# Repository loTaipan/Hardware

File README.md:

#Hardware

This repo contains the hardware design.

The idea was to have it compatible with the original pyboard, since this piece of hard and software is jus..

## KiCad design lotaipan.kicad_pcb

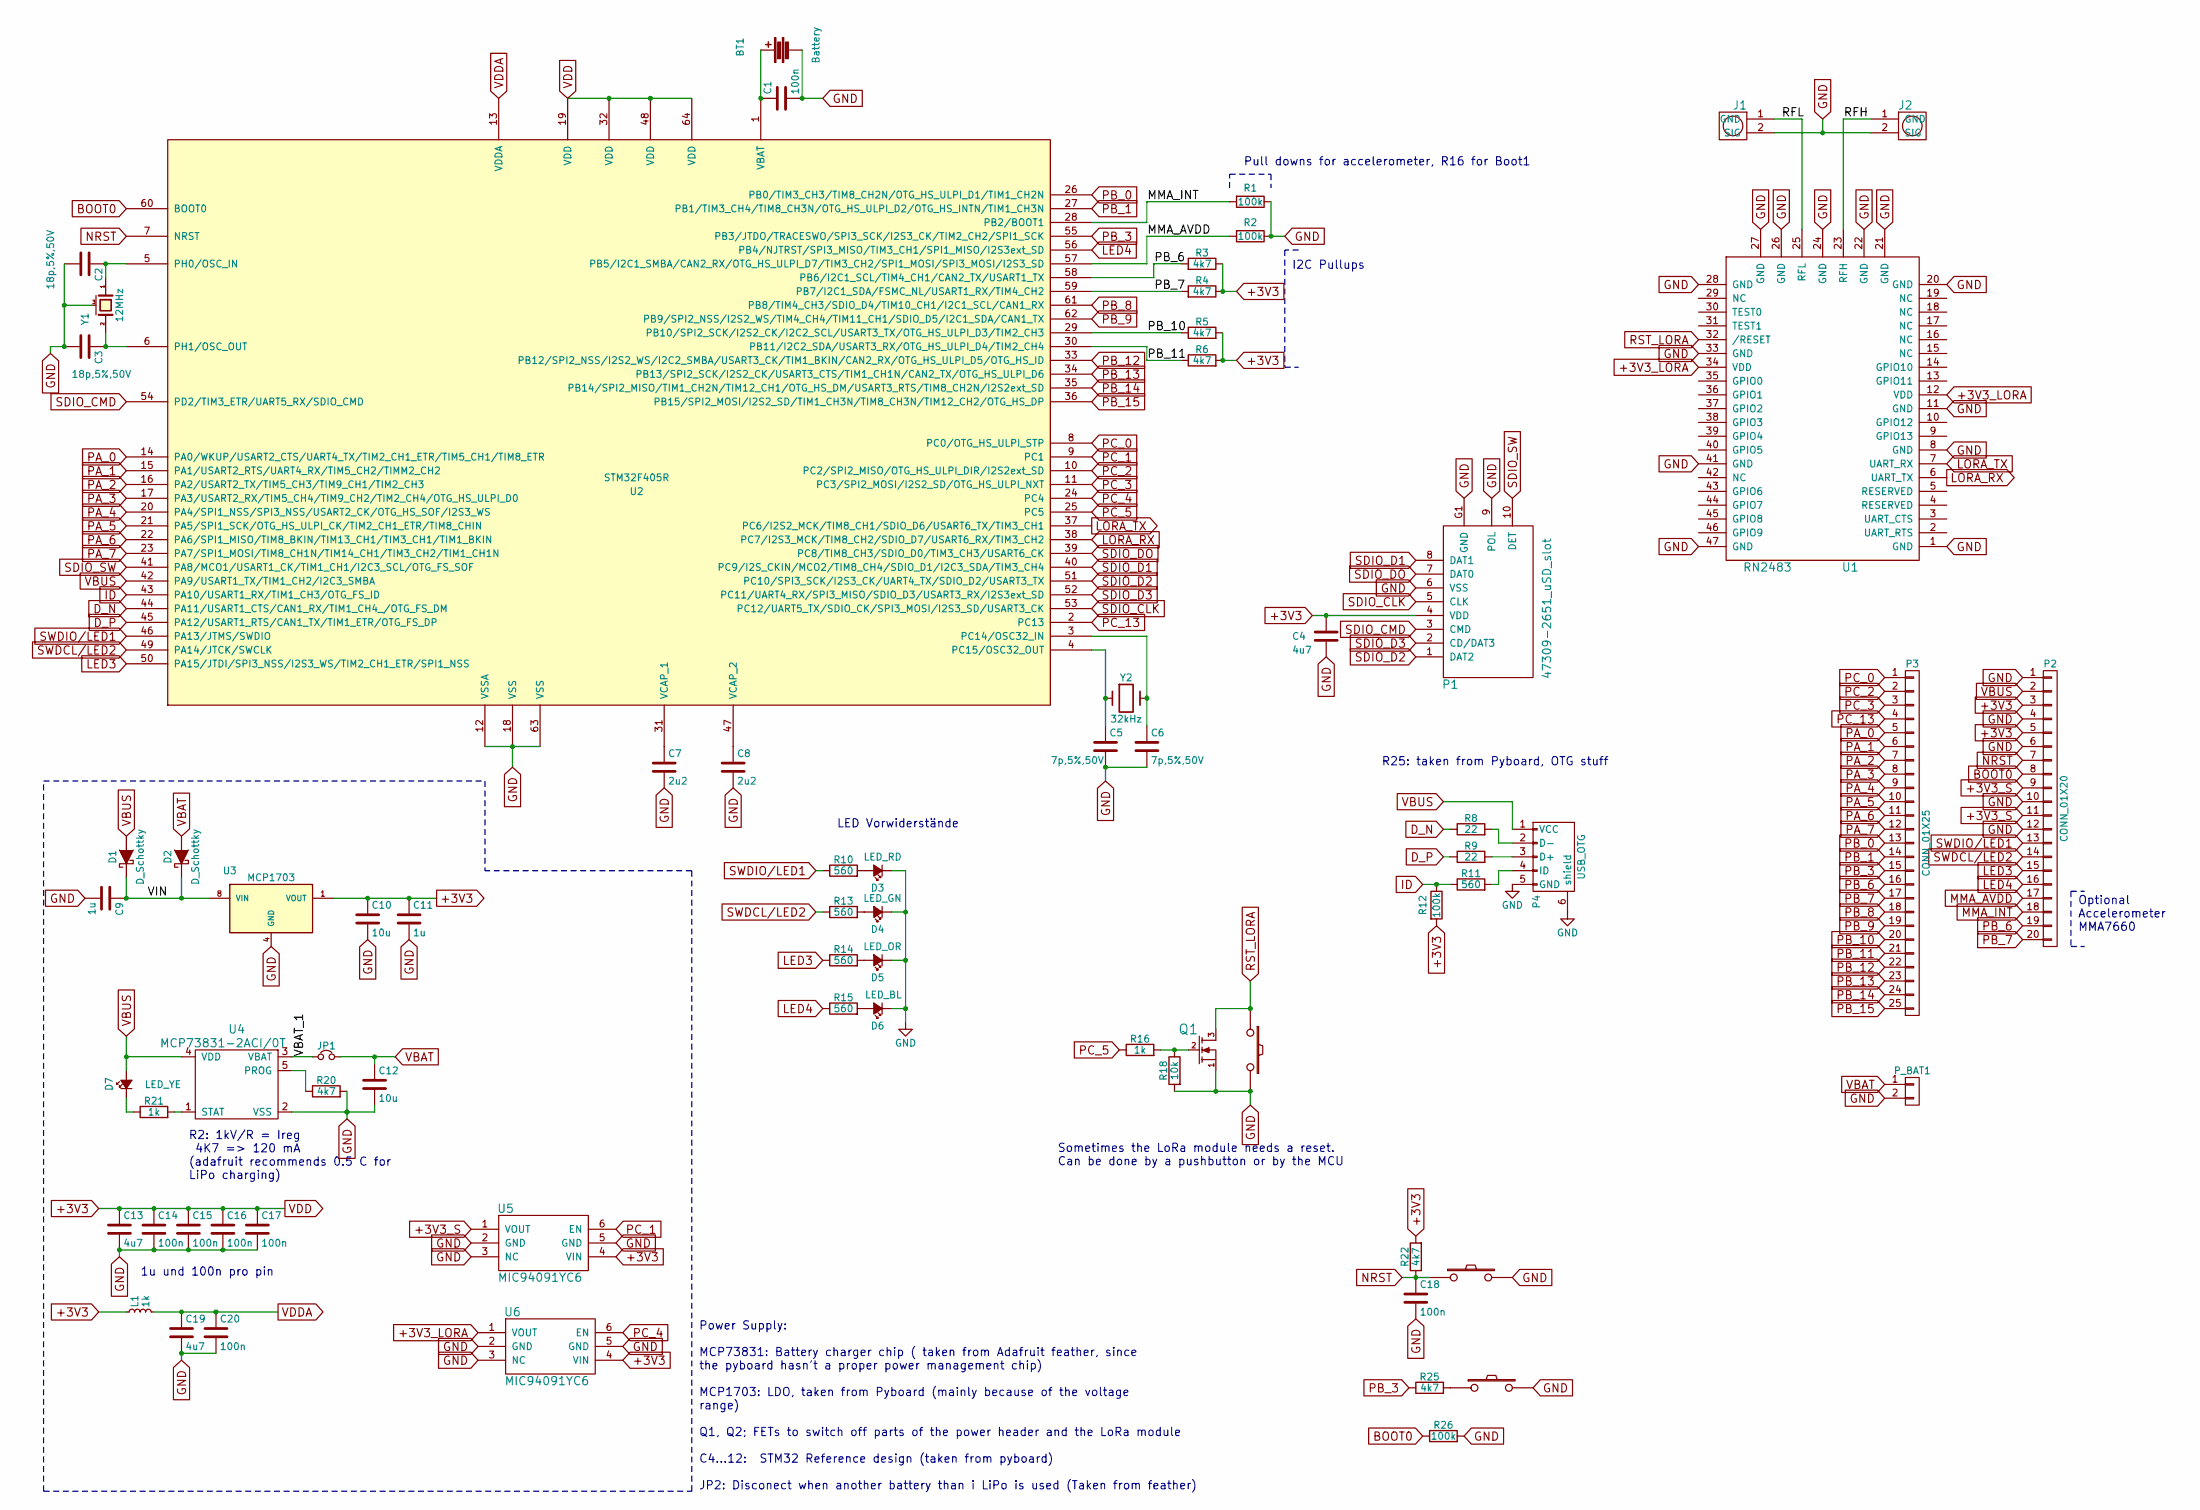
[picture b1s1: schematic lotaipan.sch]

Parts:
BT1: Battery; SparkFun-BATTERY_20MM_PTH_COMPACT
C1, C14, C15, C16, C17, C18, C20: 100n; C_0402
C2, C3: 18p,5%,50V; C_0402
C4, C13, C19: 4u7; C_0402
C5, C6: 7p,5%,50V; C_0402
C7, C8: 2u2; C_0402
C9, C11: 1u; C_0402
C10, C12: 10u; C_0402
D1, D2: D_Schottky; SOD-123
D3: LED_RD; Led_0603
D4: LED_GN; Led_0603
D5: LED_OR; Led_0603
D6: LED_BL; Led_0603
D7: LED_YE; Led_0603
J1, J2: SMA_through; coaxial_u.fl-r-smt-1
JP1: Jumper_NC_Small; SparkFun-SJ-NO
L1: 1k; inductor_smd_1008
P1: 47309-2651_uSD_slot; microsd_socket
P2: CONN_01X20; Pin_Header_Straight_1x20
P3: CONN_01X25; Pin_Header_Straight_1x25
P4: USB_OTG; conn_usb_B_micro_smd-2
P_BAT1: CONN_01X02; s2b-ph-kl
Q1: MOS_N_SGD; SOT-23
R1, R2, R12, R26: 100k; R_0402
R3, R4, R5, R6, R20, R22, R25: 4k7; R_0402
R8, R9: 22; R_0402
R10, R11, R13, R14, R15: 560; R_0402
R16, R21: 1k; R_0402
R18: 10k; R_0402
SW_RST1: SW_PUSH; smd_push
SW_RST_LORA1: SW_PUSH; smd_push
SW_USR1: SW_PUSH; smd_push
U1: RN2483
U2: STM32F405R; AB2_LQFP64
U3: MCP1703; dfn8-2x3
U4: MCP73831-2ACI/0T; sot23-5
U5, U6: MIC94091YC6; SC-70-6
Y1: 12MHz; crystal_FA238-TSX3225
Y2: 32kHz; ST3215SB32768C0HPWBB

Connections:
+3V3: C4.1, C10.1, C11.1, C13.1, C14.1, C15.1, C16.1, C17.1, L1.1, P1.4 (VDD), P2.3, P2.5, R3.1, R4.1, R5.2, R6.2, R12.2, R22.2, U2.19 (VDD), U2.32 (VDD), U2.48 (VDD), U2.64 (VDD), U3.1 (VOUT), U5.4 (VIN), U6.4 (VIN)
+3V3_LORA: U1.12 (VDD), U1.34 (VDD), U6.1 (VOUT)
+3V3_S: P2.9, P2.11, U5.1 (VOUT)
/RFH: J2.1 (GND), U1.23 (RFH)
/RFL: J1.1 (GND), U1.25 (RFL)
/VBAT_1: JP1.1, U4.3 (VBAT)
/VIN: C9.1, D1.1 (K), D2.1 (K), U3.8 (VIN)
BOOT0: P2.8, R26.1, U2.60 (BOOT0)
D_N: R8.1, U2.44 (PA11/USART1_CTS/CAN1_RX/TIM1_CH4_/OTG_F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)
D_P: R9.1, U2.45 (PA12/USART1_RTS/CAN1_TX/TIM1_ETR/OTG_FS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)
GND: BT1.2, C1.2, C2.2, C3.2, C4.2, C5.2, C6.2, C7.2, C8.2, C9.2, C10.2, C11.2, C12.2, C13.2, C14.2, C15.2, C16.2, C17.2, C18.2, C19.2, C20.2, D3.1 (K), D4.1 (K), D5.1 (K), D6.1 (K), J1.2 (SIG), J2.2 (SIG), P1.6 (VSS), P1.9 (POL), P1.G1 (GND), P2.1, P2.4, P2.6, P2.10, P2.12, P4.5 (GND), P4.6 (shield), P_BAT1.2, Q1.1 (S), R1.1, R2.1, R18.2, R20.2, R26.2, SW_RST1.2, SW_RST_LORA1.2, SW_USR1.2, U1.1 (GND), U1.8 (GND), U1.11 (GND), U1.20 (GND), U1.21 (GND), U1.22 (GND), U1.24 (GND), U1.26 (GND), U1.27 (GND), U1.28 (GND), U1.33 (GND), U1.41 (GND), U1.47 (GND), U2.12 (VSSA), U2.18 (VSS), U2.63 (VSS), U3.4 (GND), U4.2 (VSS), U5.2 (GND), U5.3 (NC), U5.5 (GND), U6.2 (GND), U6.3 (NC), U6.5 (GND), Y1.3 (case)
ID: R11.1, R12.1, U2.43 (PA10/USART1_RX/TIM1_CH3/OTG_FS_ID)
LED3: P2.15, R14.1, U2.50 (PA15/JTDI/SPI3_NSS/I2S3_WS/TIM2_CH1_ETR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)
LED4: P2.16, R15.1, U2.56 (PB4/NJTRST/SPI3_MISO/TIM3_CH1/SPI1_MISO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)
LORA_RX: U1.6 (UART_TX), U2.38 (PC7/I2S3_MCK/TIM8_CH2/SDIO_D7/USART6_RX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)
LORA_TX: U1.7 (UART_RX), U2.37 (PC6/I2S2_MCK/TIM8_CH1/SDIO_D6/USART6_TX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)
MMA_AVDD: P2.17, R2.2, U2.57 (PB5/I2C1_SMBA/CAN2_RX/OTG_HS_ULPI_D7/TI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)
MMA_INT: P2.18, R1.2, U2.28 (PB2/BOOT1)
NRST: C18.1, P2.7, R22.1, SW_RST1.1, U2.7 (NRST)
unnamed: BT1.1, C1.1, U2.1 (VBAT)
unnamed: C2.1, U2.5 (PH0/OSC_IN), Y1.1
unnamed: C3.1, U2.6 (PH1/OSC_OUT), Y1.2
unnamed: C5.1, U2.4 (PC15/OSC32_OUT), Y2.1
unnamed: C6.1, U2.3 (PC14/OSC32_IN), Y2.2
unnamed: C7.1, U2.31 (VCAP_1)
unnamed: C8.1, U2.47 (VCAP_2)
unnamed: D3.2 (A), R10.2
unnamed: D4.2 (A), R13.2
unnamed: D5.2 (A), R14.2
unnamed: D6.2 (A), R15.2
unnamed: D7.1 (K), R21.1
unnamed: P4.2 (D-), R8.2
unnamed: P4.3 (D+), R9.2
unnamed: P4.4 (ID), R11.2
unnamed: Q1.2 (G), R16.2, R18.1
unnamed: R20.1, U4.5 (PROG)
unnamed: R21.2, U4.1 (STAT)
unnamed: R25.2, SW_USR1.1
PA_0: P3.5, U2.14 (PA0/WKUP/USART2_CTS/UART4_TX/TIM2_CH1_E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)
PA_1: P3.6, U2.15 (PA1/USART2_RTS/UART4_RX/TIM5_CH2/TIMM2_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)
PA_2: P3.7, U2.16 (PA2/USART2_TX/TIM5_CH3/TIM9_CH1/TIM2_CH3)
PA_3: P3.8, U2.17 (PA3/USART2_RX/TIM5_CH4/TIM9_CH2/TIM2_CH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)
PA_4: P3.9, U2.20 (PA4/SPI1_NSS/SPI3_NSS/USART2_CK/OTG_HS_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)
PA_5: P3.10, U2.21 (PA5/SPI1_SCK/OTG_HS_ULPI_CK/TIM2_CH1_ET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)
PA_6: P3.11, U2.22 (PA6/SPI1_MISO/TIM8_BKIN/TIM13_CH1/TIM3_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)
PA_7: P3.12, U2.23 (PA7/SPI1_MOSI/TIM8_CH1N/TIM14_CH1/TIM3_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)
PB_0: P3.13, U2.26 (PB0/TIM3_CH3/TIM8_CH2N/OTG_HS_ULPI_D1/T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)
PB_1: P3.14, U2.27 (PB1/TIM3_CH4/TIM8_CH3N/OTG_HS_ULPI_D2/O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)
PB_3: P3.15, R25.1, U2.55 (PB3/JTDO/TRACESWO/SPI3_SCK/I2S3_CK/TIM2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)
PB_6: P2.19, P3.16, R3.2, U2.58 (PB6/I2C1_SCL/TIM4_CH1/CAN2_TX/USART1_TX)
PB_7: P2.20, P3.17, R4.2, U2.59 (PB7/I2C1_SDA/FSMC_NL/USART1_RX/TIM4_CH2)
PB_8: P3.18, U2.61 (PB8/TIM4_CH3/SDIO_D4/TIM10_CH1/I2C1_SCL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)
PB_9: P3.19, U2.62 (PB9/SPI2_NSS/I2S2_WS/TIM4_CH4/TIM11_CH1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)
PB_10: P3.20, R5.1, U2.29 (PB10/SPI2_SCK/I2S2_CK/I2C2_SCL/USART3_T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)
PB_11: P3.21, R6.1, U2.30 (PB11/I2C2_SDA/USART3_RX/OTG_HS_ULPI_D4/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)
PB_12: P3.22, U2.33 (PB12/SPI2_NSS/I2S2_WS/I2C2_SMBA/USART3_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)
PB_13: P3.23, U2.34 (PB13/SPI2_SCK/I2S2_CK/USART3_CTS/TIM1_C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)
PB_14: P3.24, U2.35 (PB14/SPI2_MISO/TIM1_CH2N/TIM12_CH1/OTG_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)
PB_15: P3.25, U2.36 (PB15/SPI2_MOSI/I2S2_SD/TIM1_CH3N/TIM8_C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)
PC_0: P3.1, U2.8 (PC0/OTG_HS_ULPI_STP)
PC_1: U2.9 (PC1), U5.6 (EN)
PC_2: P3.2, U2.10 (PC2/SPI2_MISO/OTG_HS_ULPI_DIR/I2S2ext_SD)
PC_3: P3.3, U2.11 (PC3/SPI2_MOSI/I2S2_SD/OTG_HS_ULPI_NXT)
PC_4: U2.24 (PC4), U6.6 (EN)
PC_5: R16.1, U2.25 (PC5)
PC_13: P3.4, U2.2 (PC13)
RST_LORA: Q1.3 (D), SW_RST_LORA1.1, U1.32 (/RESET)
SDIO_CLK: P1.5 (CLK), U2.53 (PC12/UART5_TX/SDIO_CK/SPI3_MOSI/I2S3_SD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)
SDIO_CMD: P1.3 (CMD), U2.54 (PD2/TIM3_ETR/UART5_RX/SDIO_CMD)
SDIO_D1: P1.8 (DAT1), U2.40 (PC9/I2S_CKIN/MCO2/TIM8_CH4/SDIO_D1/I2C3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)
SDIO_D2: P1.1 (DAT2), U2.51 (PC10/SPI3_SCK/I2S3_CK/UART4_TX/SDIO_D2/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)
SDIO_D3: P1.2 (CD/DAT3), U2.52 (PC11/UART4_RX/SPI3_MISO/SDIO_D3/USART3_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)
SDIO_DO: P1.7 (DAT0), U2.39 (PC8/TIM8_CH3/SDIO_D0/TIM3_CH3/USART6_CK)
SDIO_SW: P1.10 (DET), U2.41 (PA8/MCO1/USART1_CK/TIM1_CH1/I2C3_SCL/OT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)
SWDCL/LED2: P2.14, R13.1, U2.49 (PA14/JTCK/SWCLK)
SWDIO/LED1: P2.13, R10.1, U2.46 (PA13/JTMS/SWDIO)
VBAT: C12.1, D2.2 (A), JP1.2, P_BAT1.1
VDDA: C19.1, C20.1, L1.2, U2.13 (VDDA)

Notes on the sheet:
Power Supply: MCP73831: Battery charger chip ( taken from Adafruit feather, since the pyboard hasn't a proper power management chip) MCP1703: LDO, taken from Pyboard (mainly because of the voltage range) Q1, Q2; FETs to switch off parts of the power header and the LoRa module C4...12: STM32 Referen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
Optional Accelerometer MMA7660
R2: 1kV/R = Ireg 4K7 => 120 mA (adafruit recommends 0.5 C for LiPo charging)
R25: taken from Pyboard, OTG stuff
Sometimes the LoRa module needs a reset. Can be done by a pushbutton or by the MCU
I2C Pullups
Pull downs for accelerometer, R16 for Boot1
LED Vorwiderstände
1u und 100n pro pin

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
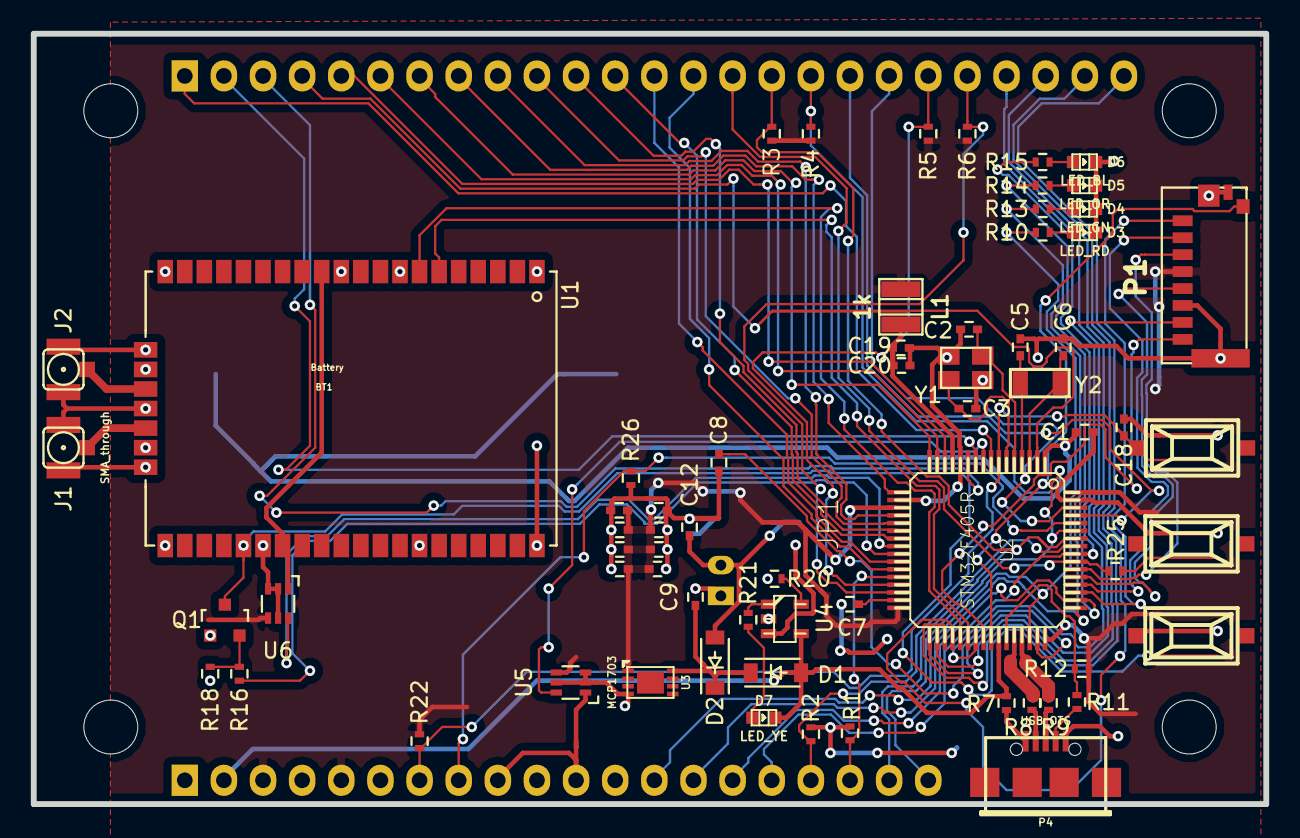
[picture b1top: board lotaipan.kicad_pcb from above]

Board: 4 copper layers, 80.0 x 50.0 mm, 71 parts (0 on the bottom side), 80 nets.

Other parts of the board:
R7: 560; R_0402

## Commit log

2016-09-13 Fixes and images
2016-10-02 Notes in schematics
    Layout schould be updated
